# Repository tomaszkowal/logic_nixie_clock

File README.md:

Do you want to build a nixie clock, but you are tired of code writing being associated with AI vibe coding? Or perhaps you never like to write code, just like me? Or you just want to do things differently and want to use some half a century old CMOS technology?
Then perhaps this clock project is just for you!

Key project ideas:
1. Is a clock
2. Uses nixie tubes as display, IN-12, ZM118x or other rectangular top view with same pinout
3. No programmable ICs
4. ICs must be from 4000 series logic
5. Other semiconductors allowed are diodes and transistors
6. Uses mains frequency for base clock source
7. Supply provided by two back to back transformers, both low and high voltages isolated from mains
8. Has a backup voltage supply which should last about a day
9. Has a backup 32768 Hz crystal oscillator with automatic clock switchover in event of mains power loss 
10. Support for 50 and 60 Hz mains
11. Support for 12hr and 24hr standards
12. AM/PM indication via separate neon bulbs or PM indication using decimal point of tens of hours tube
13. 1 Hz, 50% duty cycle blinking colons or constantly lit colons, support for separate neons or decimal points in tubes
14. Uses SOIC, SOT-23 and 0805 packages whenever possible - SMD, but easy to solder
15. Hacky technicques of mounting components* permitted
*for example, soldering a capacitor with 1-2 mm standoff to avoid contact with another THT pad 

Project status (as of 22.10.2026): rev 1.0 was manufactured, few minor issues were spotted. Rev 1.1 is being manufactured right now. Once rev 1.1 passes electrical testing, a 3D printed case will be designed. Files for the case will be added to the project repository. 
After that, a short guide on soldering and assembling the clock will be created. A broader and less chaotic feature description will be provided too. 

Project was born thanks to NiceThingsGuy who provoked me to make my own take at a microcontrolerless clock. 
Project has been inspired by other logic clocks which have been described on various blogs, especially by http://www.mcamafia.de/nixie/ncp_en/ncp.htm . I have based the ways method of US clock variant (not tested) and 32 kHz clock source are implemented on mcamafias project. I have undoubtfully been inspired by more blogposts (like danyk.cz's several logic clocks) but can't name any other specifically for any specific part of my circuit, so credits go to all of you lovely people who share your designs and ideas online. 
I don't think I have seen the dual clock method and automatic switchover in any of the designs - they were all either mains or 32 kHz oscillator based. I personally think that even best trimmed and temperature compensated crystal cannot beat EU grid frequency stability in the long term, but I also absolutely hate having to set every mains clocked clock after even brief power disruptions. Hence I implemented a supercapacitor (two dual supercaps in series, in fact) to keep just the logic part powered for a while and a local clock source in form of a classic 32 kHz crystal oscillator to keep the clock running. 
Due to startup period of a crystal oscillator it is kept running at all times - but the D flip flop doing the last /2 division is kept in steady state by presence of mains voltage.
Precision of the 32 kHz oscillator is worse than mains frequency on the long run, and the switchover is not perfect, introducing up to a second of error, but for a home clock it is generally fine - definitely better than having the clock reset to 00:00:00. Rev 1.0 tests show 24+ hours of operation on the backup supply.

The controls are fairly simple: three buttons allow to add seconds, minutes and hours (1 click = increment the counter by 1), a button to reset the clock to 00:00:00, and a button which halts the mains clock source. This allows for a sub second clock setting - allowing you to sync the second increment moment be matched to other clock. 
Warnings:
1. The buttons are functional when the clock is running on backup
2. Due to way they are introduced into the counter system, the add second/minute/hour buttons are active press/release depending on state of the clock. The most intuitive way to use them is to do short presses

Licensing:
Look, I am new to the concept of open hardware licenses. None seems to describe what I consider to be a fair, permissive open source license which would still protect me from blatant abuse.
I therefore apply a simple ruleset written in simple words for using files within this repository:
1. Do not use provided files in direct, unmodified way for profit 
2. You are free to manufacture the PCBs from files provided, assemble them and use the resulting clock for your own use or gift them to other people
3. You are free to manufacture multiple PCBs from files provided, and sell excess PCBs for price not exceeding cost of individual PCB in the production run
4. You are free to take the concept and make your own version of it on a ruleset of your choice, including closed and/or commercial use - I do not impose any inheritance of licensing rules on you (i.e. no ShareAlike), as long as your design has clearly had your input
5. When sharing this projects files, please do so by providing link to the github repository rather than sending individual files
6. I take no responsibility for any damages resulting from your use of this repository. I designed this clock in a way to make it as safe as possible and compliant with IPC norms regarding clearance and creepage (especially mains-to-the-rest-of-the-circuit), but in the end this is not a certified product, so you have to judge whether you trust me, a random person from the internet, to know what I am doing. I also do not take responsibility for your PCB quality, part choices, soldering and PCB cleaning skills.
The design involves lethal voltages and if you act irresponsibly around it, you might get hurt - or worse. I obviously do not take responsibility for that.
There are no exceptions to rule 6. If you find my design dangerous and/or not compliant with any norms, you are free (and encouraged to) open an issue on github. I will gladly take the criticism, but still - I take no responsibility.

So, you are free to do anything you want with this design EXCEPT for directly taking files from this repository as they are, manufacturing the clock or part(s) of it and selling it/them for profit. Put some effort in it if you want to make money.

Otherwise, I highly encourage you to play around and build your own clock(s) based on my ideas. 
Don't like the weird assembly? Make your own PCB! 
Don't like the tube type? Make your own PCB, or even a sandwich of two so you can swap tube types! 
Don't like SMD? All of parts used exist in THT variants! 
You can also go the other way around and use TSSOP ICs and smaller passive packages. You can change socket type. You can move this to 7400 series logic. You can change whatever you don't like about this project! 

This project is proudly 0% AI.

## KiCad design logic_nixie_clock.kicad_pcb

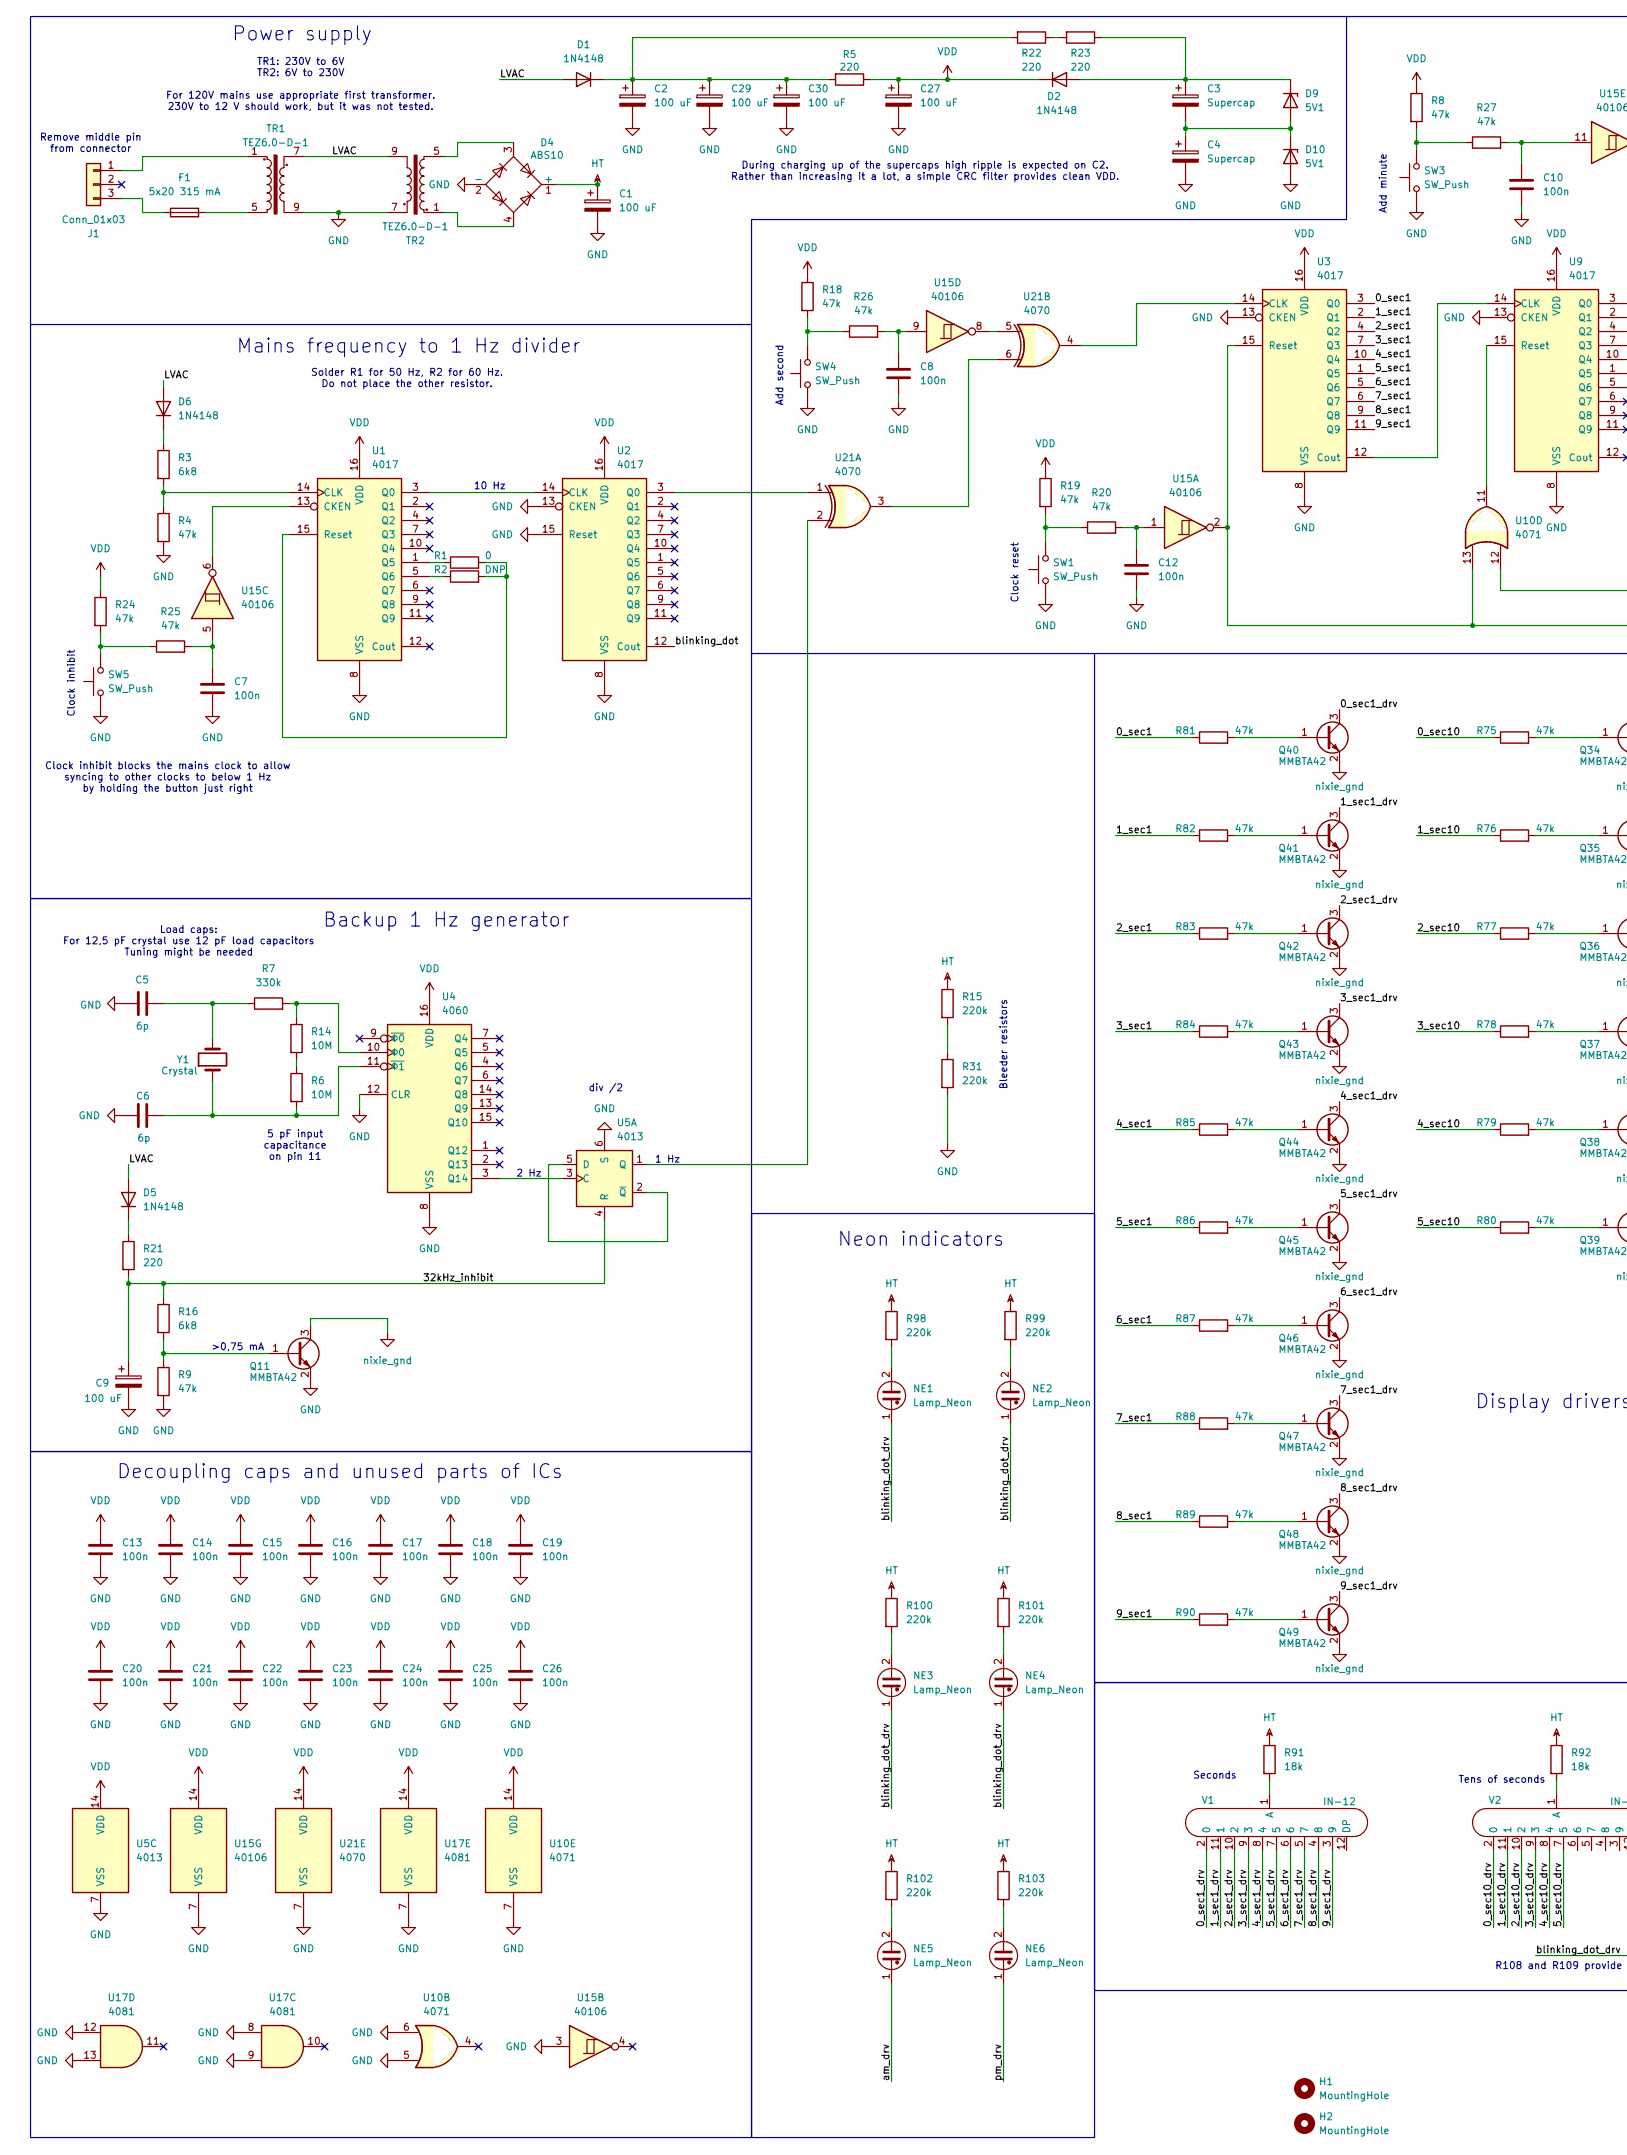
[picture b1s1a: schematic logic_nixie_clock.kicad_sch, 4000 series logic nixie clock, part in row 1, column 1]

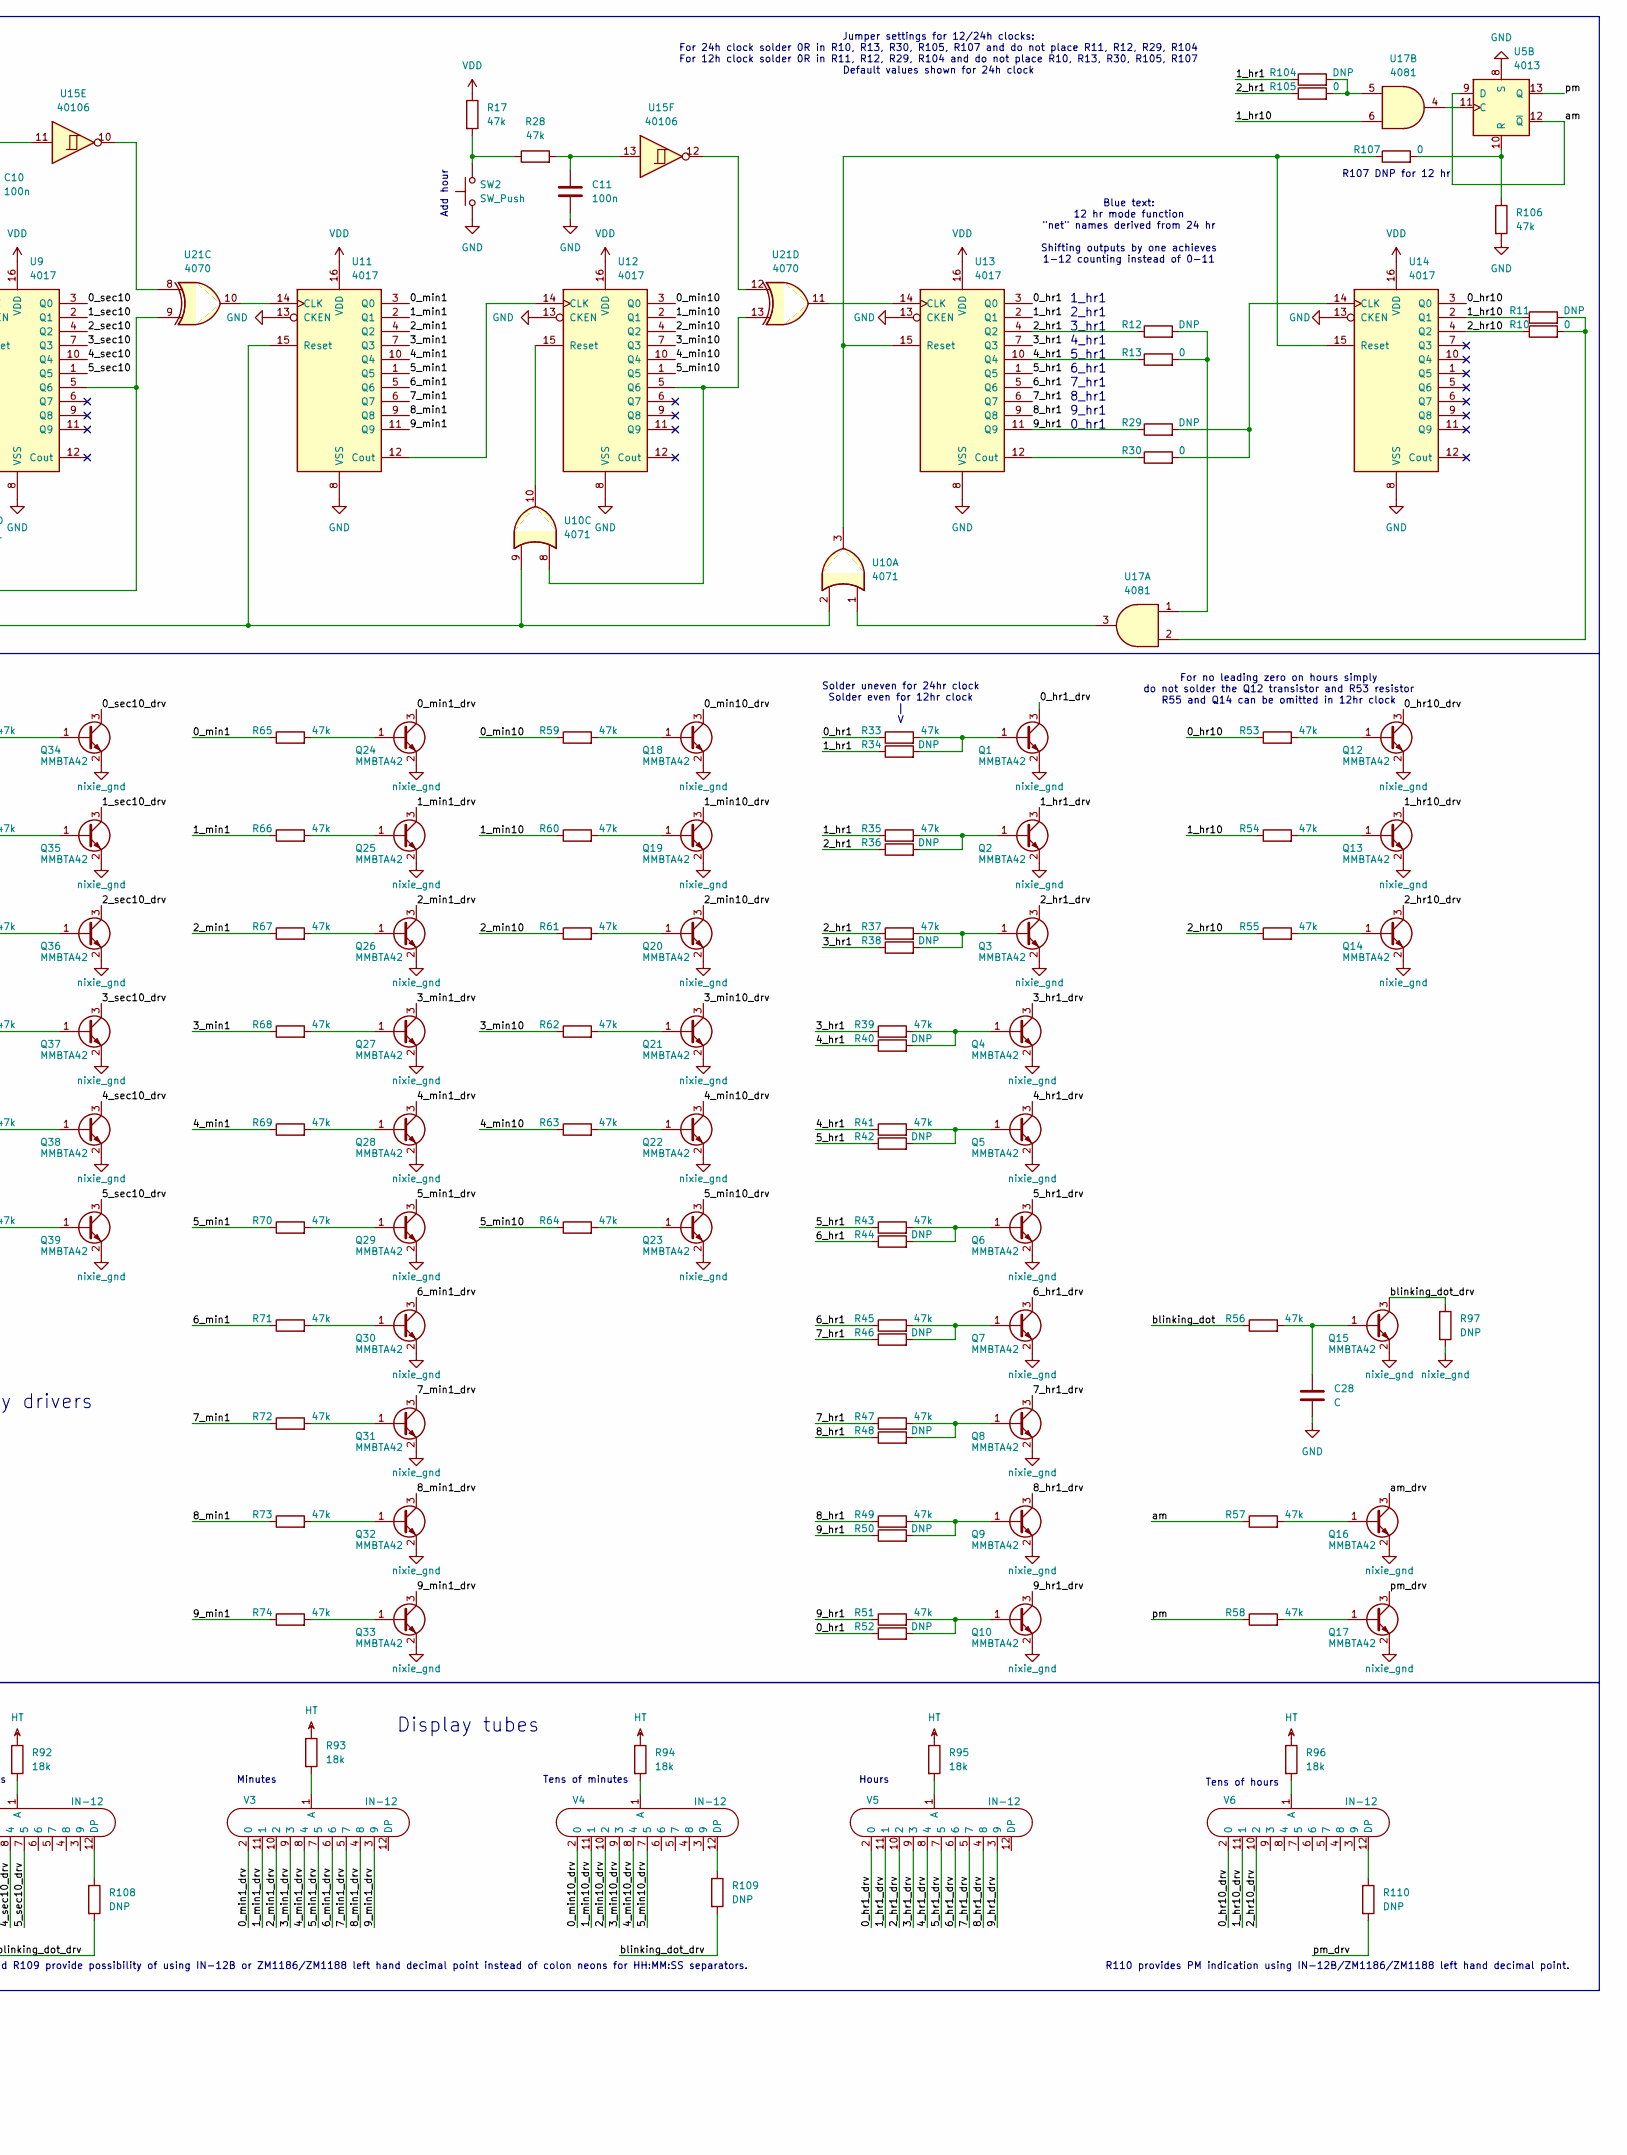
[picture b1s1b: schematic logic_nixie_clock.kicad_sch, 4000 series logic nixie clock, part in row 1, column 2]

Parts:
C1: 100 uF; CP_Radial_D16.0mm_P7.50mm
C2, C9, C27, C29, C30: 100 uF; CP_Radial_D5.0mm_P2.00mm
C3, C4: Supercap; 17x25x8,5mm double supercapacitor
C5, C6: 6p; C_0805_2012Metric_Pad1.18x1.45mm_HandSolder
C7, C8, C10, C11, C12, C13, C14, C15, C16, C17, C18, C19, C20, C21, C22, C23, C24, C25, C26: 100n; C_0805_2012Metric_Pad1.18x1.45mm_HandSolder
C28: C; C_0805_2012Metric_Pad1.18x1.45mm_HandSolder
D1, D2, D5, D6: 1N4148; D_SOD-123F
D4: ABS10; Diode_Bridge_Diotec_ABS
D9, D10: 5V1; D_MiniMELF
F1: 5x20 315 mA; Fuseholder_Clip-5x20mm_Schurter_CQM_Inline_P20.60x5.00mm_D1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
H1, H2: MountingHole; MountingHole_3.2mm_M3
J1: Conn_01x03; JST_VH_B3P-VH-B_1x03_P3.96mm_Vertical
NE1, NE2, NE3, NE4, NE5, NE6: Lamp_Neon; NE-2 4mm
Q1, Q2, Q3, Q4, Q5, Q6, Q7, Q8, Q9, Q10, Q11, Q12, Q13, Q14, Q15, Q16, Q17, Q18, Q19, Q20, Q21, Q22, Q23, Q24, Q25, Q26, Q27, Q28, Q29, Q30, Q31, Q32, Q33, Q34, Q35, Q36, Q37, Q38, Q39, Q40, Q41, Q42, Q43, Q44, Q45, Q46, Q47, Q48, Q49: MMBTA42; SOT-23-3
R1, R10, R13, R30, R105, R107: 0; R_0805_2012Metric_Pad1.20x1.40mm_HandSolder
R2, R11, R12, R29, R34, R36, R38, R40, R42, R44, R46, R48, R50, R52, R97, R104: DNP; R_0805_2012Metric_Pad1.20x1.40mm_HandSolder
R3, R16: 6k8; R_0805_2012Metric_Pad1.20x1.40mm_HandSolder
R4, R8, R9, R17, R18, R19, R20, R24, R25, R26, R27, R28, R33, R35, R37, R39, R41, R43, R45, R47, R49, R51, R53, R54, R55, R56, R57, R58, R59, R60, R61, R62, R63, R64, R65, R66, R67, R68, R69, R70, R71, R72, R73, R74, R75, R76, R77, R78, R79, R80, R81, R82, R83, R84, R85, R86, R87, R88, R89, R90, R106: 47k; R_0805_2012Metric_Pad1.20x1.40mm_HandSolder
R5, R21, R22, R23: 220; R_0805_2012Metric_Pad1.20x1.40mm_HandSolder
R6, R14: 10M; R_0805_2012Metric_Pad1.20x1.40mm_HandSolder
R7: 330k; R_0805_2012Metric_Pad1.20x1.40mm_HandSolder
R15, R31, R98, R99, R100, R101, R102, R103: 220k; R_1206_3216Metric_Pad1.30x1.75mm_HandSolder
R91, R92, R93, R94, R95, R96: 18k; R_1206_3216Metric_Pad1.30x1.75mm_HandSolder
R108, R109, R110: DNP; R_1206_3216Metric_Pad1.30x1.75mm_HandSolder
SW1, SW2, SW3, SW4, SW5: SW_Push; SW_Tactile_SPST_Angled_PTS645Vx58-2LFS
TR1, TR2: TEZ6.0-D-1; Transformer_Breve_TEZ-38x45
U1, U2, U3, U9, U11, U12, U13, U14: 4017; SO-16_3.9x9.9mm_P1.27mm
U4: 4060; SO-16_3.9x9.9mm_P1.27mm
U5: 4013; SO-14_3.9x8.65mm_P1.27mm
U10: 4071; SO-14_3.9x8.65mm_P1.27mm
U15: 40106; SO-14_3.9x8.65mm_P1.27mm
U17: 4081; SO-14_3.9x8.65mm_P1.27mm
U21: 4070; SO-14_3.9x8.65mm_P1.27mm
V1, V2, V3, V4, V5, V6: IN-12; IN-12_ZM1180_universal
Y1: Crystal; Crystal_C38-LF_D3.0mm_L8.0mm_Vertical

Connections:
/0_hr1: R33.1, R52.1, U13.3 (Q0)
/0_hr1_drv: Q1.3 (C), V5.2 (0)
/0_hr10: R53.1, U14.3 (Q0)
/0_hr10_drv: Q12.3 (C), V6.2 (0)
/0_min1: R65.1, U11.3 (Q0)
/0_min1_drv: Q24.3 (C), V3.2 (0)
/0_min10: R59.1, U12.3 (Q0)
/0_min10_drv: Q18.3 (C), V4.2 (0)
/0_sec1: R81.1, U3.3 (Q0)
/0_sec1_drv: Q40.3 (C), V1.2 (0)
/0_sec10: R75.1, U9.3 (Q0)
/0_sec10_drv: Q34.3 (C), V2.2 (0)
/1_hr1: R34.1, R35.1, R104.1, U13.2 (Q1)
/1_hr1_drv: Q2.3 (C), V5.11 (1)
/1_hr10: R11.1, R54.1, U14.2 (Q1), U17.6
/1_hr10_drv: Q13.3 (C), V6.11 (1)
/1_min1: R66.1, U11.2 (Q1)
/1_min1_drv: Q25.3 (C), V3.11 (1)
/1_min10: R60.1, U12.2 (Q1)
/1_min10_drv: Q19.3 (C), V4.11 (1)
/1_sec1: R82.1, U3.2 (Q1)
/1_sec1_drv: Q41.3 (C), V1.11 (1)
/1_sec10: R76.1, U9.2 (Q1)
/1_sec10_drv: Q35.3 (C), V2.11 (1)
/2_hr1: R12.1, R36.1, R37.1, R105.1, U13.4 (Q2)
/2_hr1_drv: Q3.3 (C), V5.10 (2)
/2_hr10: R10.1, R55.1, U14.4 (Q2)
/2_hr10_drv: Q14.3 (C), V6.10 (2)
/2_min1: R67.1, U11.4 (Q2)
/2_min1_drv: Q26.3 (C), V3.10 (2)
/2_min10: R61.1, U12.4 (Q2)
/2_min10_drv: Q20.3 (C), V4.10 (2)
/2_sec1: R83.1, U3.4 (Q2)
/2_sec1_drv: Q42.3 (C), V1.10 (2)
/2_sec10: R77.1, U9.4 (Q2)
/2_sec10_drv: Q36.3 (C), V2.10 (2)
/3_hr1: R38.1, R39.1, U13.7 (Q3)
/3_hr1_drv: Q4.3 (C), V5.9 (3)
/3_min1: R68.1, U11.7 (Q3)
/3_min1_drv: Q27.3 (C), V3.9 (3)
/3_min10: R62.1, U12.7 (Q3)
/3_min10_drv: Q21.3 (C), V4.9 (3)
/3_sec1: R84.1, U3.7 (Q3)
/3_sec1_drv: Q43.3 (C), V1.9 (3)
/3_sec10: R78.1, U9.7 (Q3)
/3_sec10_drv: Q37.3 (C), V2.9 (3)
/4_hr1: R13.1, R40.1, R41.1, U13.10 (Q4)
/4_hr1_drv: Q5.3 (C), V5.8 (4)
/4_min1: R69.1, U11.10 (Q4)
/4_min1_drv: Q28.3 (C), V3.8 (4)
/4_min10: R63.1, U12.10 (Q4)
/4_min10_drv: Q22.3 (C), V4.8 (4)
/4_sec1: R85.1, U3.10 (Q4)
/4_sec1_drv: Q44.3 (C), V1.8 (4)
/4_sec10: R79.1, U9.10 (Q4)
/4_sec10_drv: Q38.3 (C), V2.8 (4)
/5_hr1: R42.1, R43.1, U13.1 (Q5)
/5_hr1_drv: Q6.3 (C), V5.7 (5)
/5_min1: R70.1, U11.1 (Q5)
/5_min1_drv: Q29.3 (C), V3.7 (5)
/5_min10: R64.1, U12.1 (Q5)
/5_min10_drv: Q23.3 (C), V4.7 (5)
/5_sec1: R86.1, U3.1 (Q5)
/5_sec1_drv: Q45.3 (C), V1.7 (5)
/5_sec10: R80.1, U9.1 (Q5)
/5_sec10_drv: Q39.3 (C), V2.7 (5)
/6_hr1: R44.1, R45.1, U13.5 (Q6)
/6_hr1_drv: Q7.3 (C), V5.6
/6_min1: R71.1, U11.5 (Q6)
/6_min1_drv: Q30.3 (C), V3.6
/6_sec1: R87.1, U3.5 (Q6)
/6_sec1_drv: Q46.3 (C), V1.6
/7_hr1: R46.1, R47.1, U13.6 (Q7)
/7_hr1_drv: Q8.3 (C), V5.5 (7)
/7_min1: R72.1, U11.6 (Q7)
/7_min1_drv: Q31.3 (C), V3.5 (7)
/7_sec1: R88.1, U3.6 (Q7)
/7_sec1_drv: Q47.3 (C), V1.5 (7)
/8_hr1: R48.1, R49.1, U13.9 (Q8)
/8_hr1_drv: Q9.3 (C), V5.4 (8)
/8_min1: R73.1, U11.9 (Q8)
/8_min1_drv: Q32.3 (C), V3.4 (8)
/8_sec1: R89.1, U3.9 (Q8)
/8_sec1_drv: Q48.3 (C), V1.4 (8)
/9_hr1: R29.1, R50.1, R51.1, U13.11 (Q9)
/9_hr1_drv: Q10.3 (C), V5.3 (9)
/9_min1: R74.1, U11.11 (Q9)
/9_min1_drv: Q33.3 (C), V3.3 (9)
/9_sec1: R90.1, U3.11 (Q9)
/9_sec1_drv: Q49.3 (C), V1.3 (9)
/32kHz_inhibit: C9.1, R16.1, R21.2, U5.4 (R)
/LVAC: D1.2 (A), D5.2 (A), D6.2 (A), TR1.7, TR2.9
/am: R57.1, U5.9 (D), U5.12 (~Q)
/am_drv: NE5.1, Q16.3 (C)
/blinking_dot: R56.1, U2.12 (Cout)
/blinking_dot_drv: NE1.1, NE2.1, NE3.1, NE4.1, Q15.3 (C), R97.1, R108.2, R109.2
/pm: R58.1, U5.13 (Q)
/pm_drv: NE6.1, Q17.3 (C), R110.2
GND: C1.2, C2.2, C4.2, C5.1, C6.2, C7.2, C8.2, C9.2, C10.2, C11.2, C12.2, C13.2, C14.2, C15.2, C16.2, C17.2, C18.2, C19.2, C20.2, C21.2, C22.2, C23.2, C24.2, C25.2, C26.2, C27.2, C28.2, C29.2, C30.2, D4.2 (-), D10.2 (A), Q11.2 (E), R4.2, R9.2, R31.2, R106.2, SW1.1, SW2.1, SW3.1, SW4.1, SW5.1, TR1.9, TR2.7, U1.8 (VSS), U2.8 (VSS), U2.13 (CKEN), U2.15 (Reset), U3.8 (VSS), U3.13 (CKEN), U4.8 (VSS), U4.12 (CLR), U5.6 (S), U5.7 (VSS), U5.8 (S), U9.8 (VSS), U9.13 (CKEN), U10.5, U10.6, U10.7 (VSS), U11.8 (VSS), U11.13 (CKEN), U12.8 (VSS), U12.13 (CKEN), U13.8 (VSS), U13.13 (CKEN), U14.8 (VSS), U14.13 (CKEN), U15.3, U15.7 (VSS), U17.7 (VSS), U17.8, U17.9, U17.12, U17.13, U21.7 (VSS)
HT: C1.1, D4.1 (+), R15.1, R91.1, R92.1, R93.1, R94.1, R95.1, R96.1, R98.1, R99.1, R100.1, R101.1, R102.1, R103.1
unnamed: C5.2, R7.1, Y1.2
unnamed: C7.1, R25.2, U15.5
unnamed: C8.1, R26.2, U15.9
unnamed: C10.1, R27.2, U15.11
unnamed: C11.1, R28.2, U15.13
unnamed: C12.1, R20.2, U15.1
unnamed: C2.1, C29.1, C30.1, D1.1 (K), R5.2, R22.2
unnamed: C3.1, D2.2 (A), D9.1 (K), R23.1
unnamed: D4.3, TR2.5
unnamed: D4.4, TR2.1
unnamed: D5.1 (K), R21.1
unnamed: D6.1 (K), R3.1
unnamed: C3.2, C4.1, D9.2 (A), D10.1 (K)
unnamed: F1.2, TR1.5
unnamed: J1.1, TR1.1
unnamed: F1.1, J1.3
unnamed: NE1.2, R98.2
unnamed: NE2.2, R99.2
unnamed: NE3.2, R100.2
unnamed: NE4.2, R101.2
unnamed: NE5.2, R102.2
unnamed: NE6.2, R103.2
unnamed: Q1.1 (B), R33.2, R34.2
unnamed: Q2.1 (B), R35.2, R36.2
unnamed: Q3.1 (B), R37.2, R38.2
unnamed: Q4.1 (B), R39.2, R40.2
unnamed: Q5.1 (B), R41.2, R42.2
unnamed: Q6.1 (B), R43.2, R44.2
unnamed: Q7.1 (B), R45.2, R46.2
unnamed: Q8.1 (B), R47.2, R48.2
unnamed: Q9.1 (B), R49.2, R50.2
unnamed: Q10.1 (B), R51.2, R52.2
unnamed: Q11.1 (B), R9.1, R16.2
unnamed: Q12.1 (B), R53.2
unnamed: Q13.1 (B), R54.2
unnamed: Q14.1 (B), R55.2
unnamed: C28.1, Q15.1 (B), R56.2
unnamed: Q16.1 (B), R57.2
unnamed: Q17.1 (B), R58.2
unnamed: Q18.1 (B), R59.2
unnamed: Q19.1 (B), R60.2
unnamed: Q20.1 (B), R61.2
unnamed: Q21.1 (B), R62.2
unnamed: Q22.1 (B), R63.2
unnamed: Q23.1 (B), R64.2
unnamed: Q24.1 (B), R65.2
unnamed: Q25.1 (B), R66.2
unnamed: Q26.1 (B), R67.2
unnamed: Q27.1 (B), R68.2
unnamed: Q28.1 (B), R69.2
unnamed: Q29.1 (B), R70.2
unnamed: Q30.1 (B), R71.2
unnamed: Q31.1 (B), R72.2
unnamed: Q32.1 (B), R73.2
unnamed: Q33.1 (B), R74.2
unnamed: Q34.1 (B), R75.2
unnamed: Q35.1 (B), R76.2
unnamed: Q36.1 (B), R77.2
unnamed: Q37.1 (B), R78.2
unnamed: Q38.1 (B), R79.2
unnamed: Q39.1 (B), R80.2
unnamed: Q40.1 (B), R81.2
unnamed: Q41.1 (B), R82.2
unnamed: Q42.1 (B), R83.2
unnamed: Q43.1 (B), R84.2
unnamed: Q44.1 (B), R85.2
unnamed: Q45.1 (B), R86.2
unnamed: Q46.1 (B), R87.2
unnamed: Q47.1 (B), R88.2
unnamed: Q48.1 (B), R89.2
unnamed: Q49.1 (B), R90.2
unnamed: R10.2, R11.2, U17.2
unnamed: R12.2, R13.2, U17.1
unnamed: R6.1, R14.2
unnamed: R15.2, R31.1
unnamed: R17.2, R28.1, SW2.2
unnamed: R18.2, R26.1, SW4.2
unnamed: R19.2, R20.1, SW1.2
unnamed: R22.1, R23.2
unnamed: R24.2, R25.1, SW5.2
unnamed: R8.2, R27.1, SW3.2
unnamed: R104.2, R105.2, U17.5
unnamed: U1.13 (CKEN), U15.6
unnamed: R3.2, R4.1, U1.14 (CLK)
unnamed: U1.3 (Q0), U2.14 (CLK)
unnamed: R1.1, U1.1 (Q5)
unnamed: R2.1, U1.5 (Q6)
unnamed: R1.2, R2.2, U1.15 (Reset)
unnamed: U2.3 (Q0), U21.1
unnamed: U3.14 (CLK), U21.4
unnamed: U3.12 (Cout), U9.14 (CLK)
unnamed: U4.3 (Q14), U5.3 (C)
unnamed: C6.1, R6.2, U4.11 (~Φ1), Y1.1
unnamed: R7.2, R14.1, U4.10 (Φ0)
unnamed: U5.2 (~Q), U5.5 (D)
unnamed: U5.1 (Q), U21.2
unnamed: U5.11 (C), U17.4
unnamed: R106.1, R107.2, U5.10 (R)
unnamed: U9.5 (Q6), U10.12, U21.9
unnamed: U9.15 (Reset), U10.11
unnamed: U10.1, U17.3
unnamed: U11.14 (CLK), U21.10
unnamed: U11.12 (Cout), U12.14 (CLK)
unnamed: U3.15 (Reset), U10.2, U10.9, U10.13, U11.15 (Reset), U15.2
unnamed: U10.8, U12.5 (Q6), U21.13
unnamed: U10.10, U12.15 (Reset)
unnamed: U13.14 (CLK), U21.11
unnamed: R30.1, U13.12 (Cout)
unnamed: R107.1, U10.3, U13.15 (Reset), U14.15 (Reset)
unnamed: R29.2, R30.2, U14.14 (CLK)
unnamed: U15.8, U21.5
unnamed: U15.10, U21.8
unnamed: U15.12, U21.12
unnamed: U21.3, U21.6
unnamed: R91.2, V1.1 (A)
unnamed: R92.2, V2.1 (A)
unnamed: R108.1, V2.12 (DP)
unnamed: R93.2, V3.1 (A)
unnamed: R94.2, V4.1 (A)
unnamed: R109.1, V4.12 (DP)
unnamed: R95.2, V5.1 (A)
unnamed: R96.2, V6.1 (A)
unnamed: R110.1, V6.12 (DP)
VDD: C13.1, C14.1, C15.1, C16.1, C17.1, C18.1, C19.1, C20.1, C21.1, C22.1, C23.1, C24.1, C25.1, C26.1, C27.1, D2.1 (K), R5.1, R8.1, R17.1, R18.1, R19.1, R24.1, U1.16 (VDD), U2.16 (VDD), U3.16 (VDD), U4.16 (VDD), U5.14 (VDD), U9.16 (VDD), U10.14 (VDD), U11.16 (VDD), U12.16 (VDD), U13.16 (VDD), U14.16 (VDD), U15.14 (VDD), U17.14 (VDD), U21.14 (VDD)
nixie_gnd: Q1.2 (E), Q2.2 (E), Q3.2 (E), Q4.2 (E), Q5.2 (E), Q6.2 (E), Q7.2 (E), Q8.2 (E), Q9.2 (E), Q10.2 (E), Q11.3 (C), Q12.2 (E), Q13.2 (E), Q14.2 (E), Q15.2 (E), Q16.2 (E), Q17.2 (E), Q18.2 (E), Q19.2 (E), Q20.2 (E), Q21.2 (E), Q22.2 (E), Q23.2 (E), Q24.2 (E), Q25.2 (E), Q26.2 (E), Q27.2 (E), Q28.2 (E), Q29.2 (E), Q30.2 (E), Q31.2 (E), Q32.2 (E), Q33.2 (E), Q34.2 (E), Q35.2 (E), Q36.2 (E), Q37.2 (E), Q38.2 (E), Q39.2 (E), Q40.2 (E), Q41.2 (E), Q42.2 (E), Q43.2 (E), Q44.2 (E), Q45.2 (E), Q46.2 (E), Q47.2 (E), Q48.2 (E), Q49.2 (E), R97.2

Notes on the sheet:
Tens of hours
Minutes
R107 DNP for 12 hr
Solder uneven for 24hr clock Solder even for 12hr clock | V
Decoupling caps and unused parts of ICs
Backup 1 Hz generator
Add minute
R108 and R109 provide possibility of using IN-12B or ZM1186/ZM1188 left hand decimal point instead of colon neons for HH:MM:SS separators.
Tens of minutes
1_hr1 2_hr1 3_hr1 4_hr1 5_hr1 6_hr1 7_hr1 8_hr1 9_hr1 0_hr1
Load caps: For 12,5 pF crystal use 12 pF load capacitors Tuning might be needed
>0,75 mA
Solder R1 for 50 Hz, R2 for 60 Hz. Do not place the other resistor.
Bleeder resistors
Add hour
div /2
Blue text: 12 hr mode function "net" names derived from 24 hr Shifting outputs by one achieves 1-12 counting instead of 0-11
Neon indicators
Tens of seconds
Clock inhibit
2 Hz
TR1: 230V to 6V TR2: 6V to 230V For 120V mains use appropriate first transformer. 230V to 12 V should work, but it was not tested.
Jumper settings for 12/24h clocks: For 24h clock solder 0R in R10, R13, R30, R105, R107 and do not place R11, R12, R29, R104 For 12h clock solder 0R in R11, R12, R29, R104 and do not place R10, R13, R30, R105, R107 Default values shown for 24h clock
Power supply
Display drivers
10 Hz
Display tubes
5 pF input capacitance on pin 11
For no leading zero on hours simply do not solder the Q12 transistor and R53 resistor R55 and Q14 can be omitted in 12hr clock
Hours
During charging up of the supercaps high ripple is expected on C2. Rather than increasing it a lot, a simple CRC filter provides clean VDD.
Mains frequency to 1 Hz divider
Add second
Clock inhibit blocks the mains clock to allow syncing to other clocks to below 1 Hz by holding the button just right
Remove middle pin from connector
Seconds
R110 provides PM indication using IN-12B/ZM1186/ZM1188 left hand decimal point.
1 Hz
Clock reset

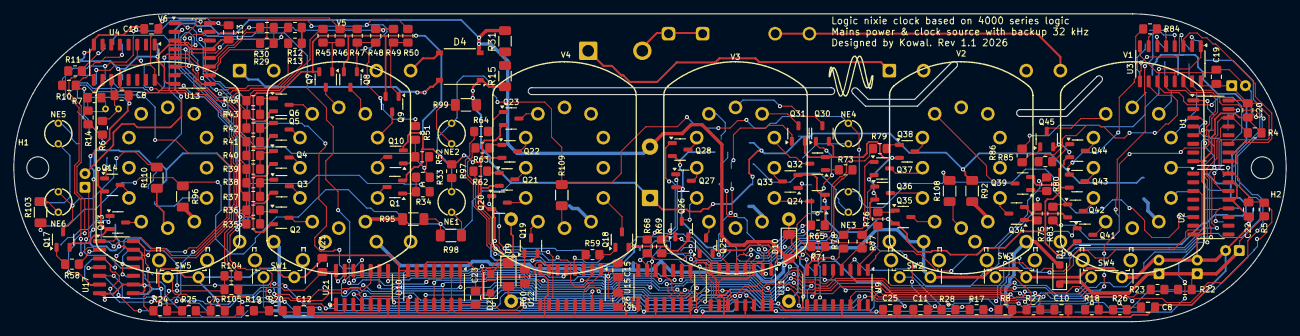
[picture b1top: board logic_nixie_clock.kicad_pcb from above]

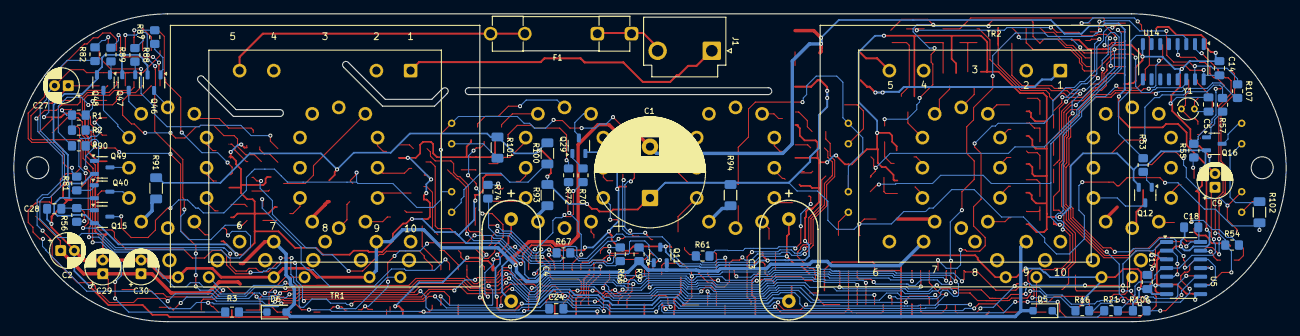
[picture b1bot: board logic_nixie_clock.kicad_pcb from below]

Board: 2 copper layers, 186.0 x 45.0 mm, 233 parts (64 on the bottom side), 225 nets.
